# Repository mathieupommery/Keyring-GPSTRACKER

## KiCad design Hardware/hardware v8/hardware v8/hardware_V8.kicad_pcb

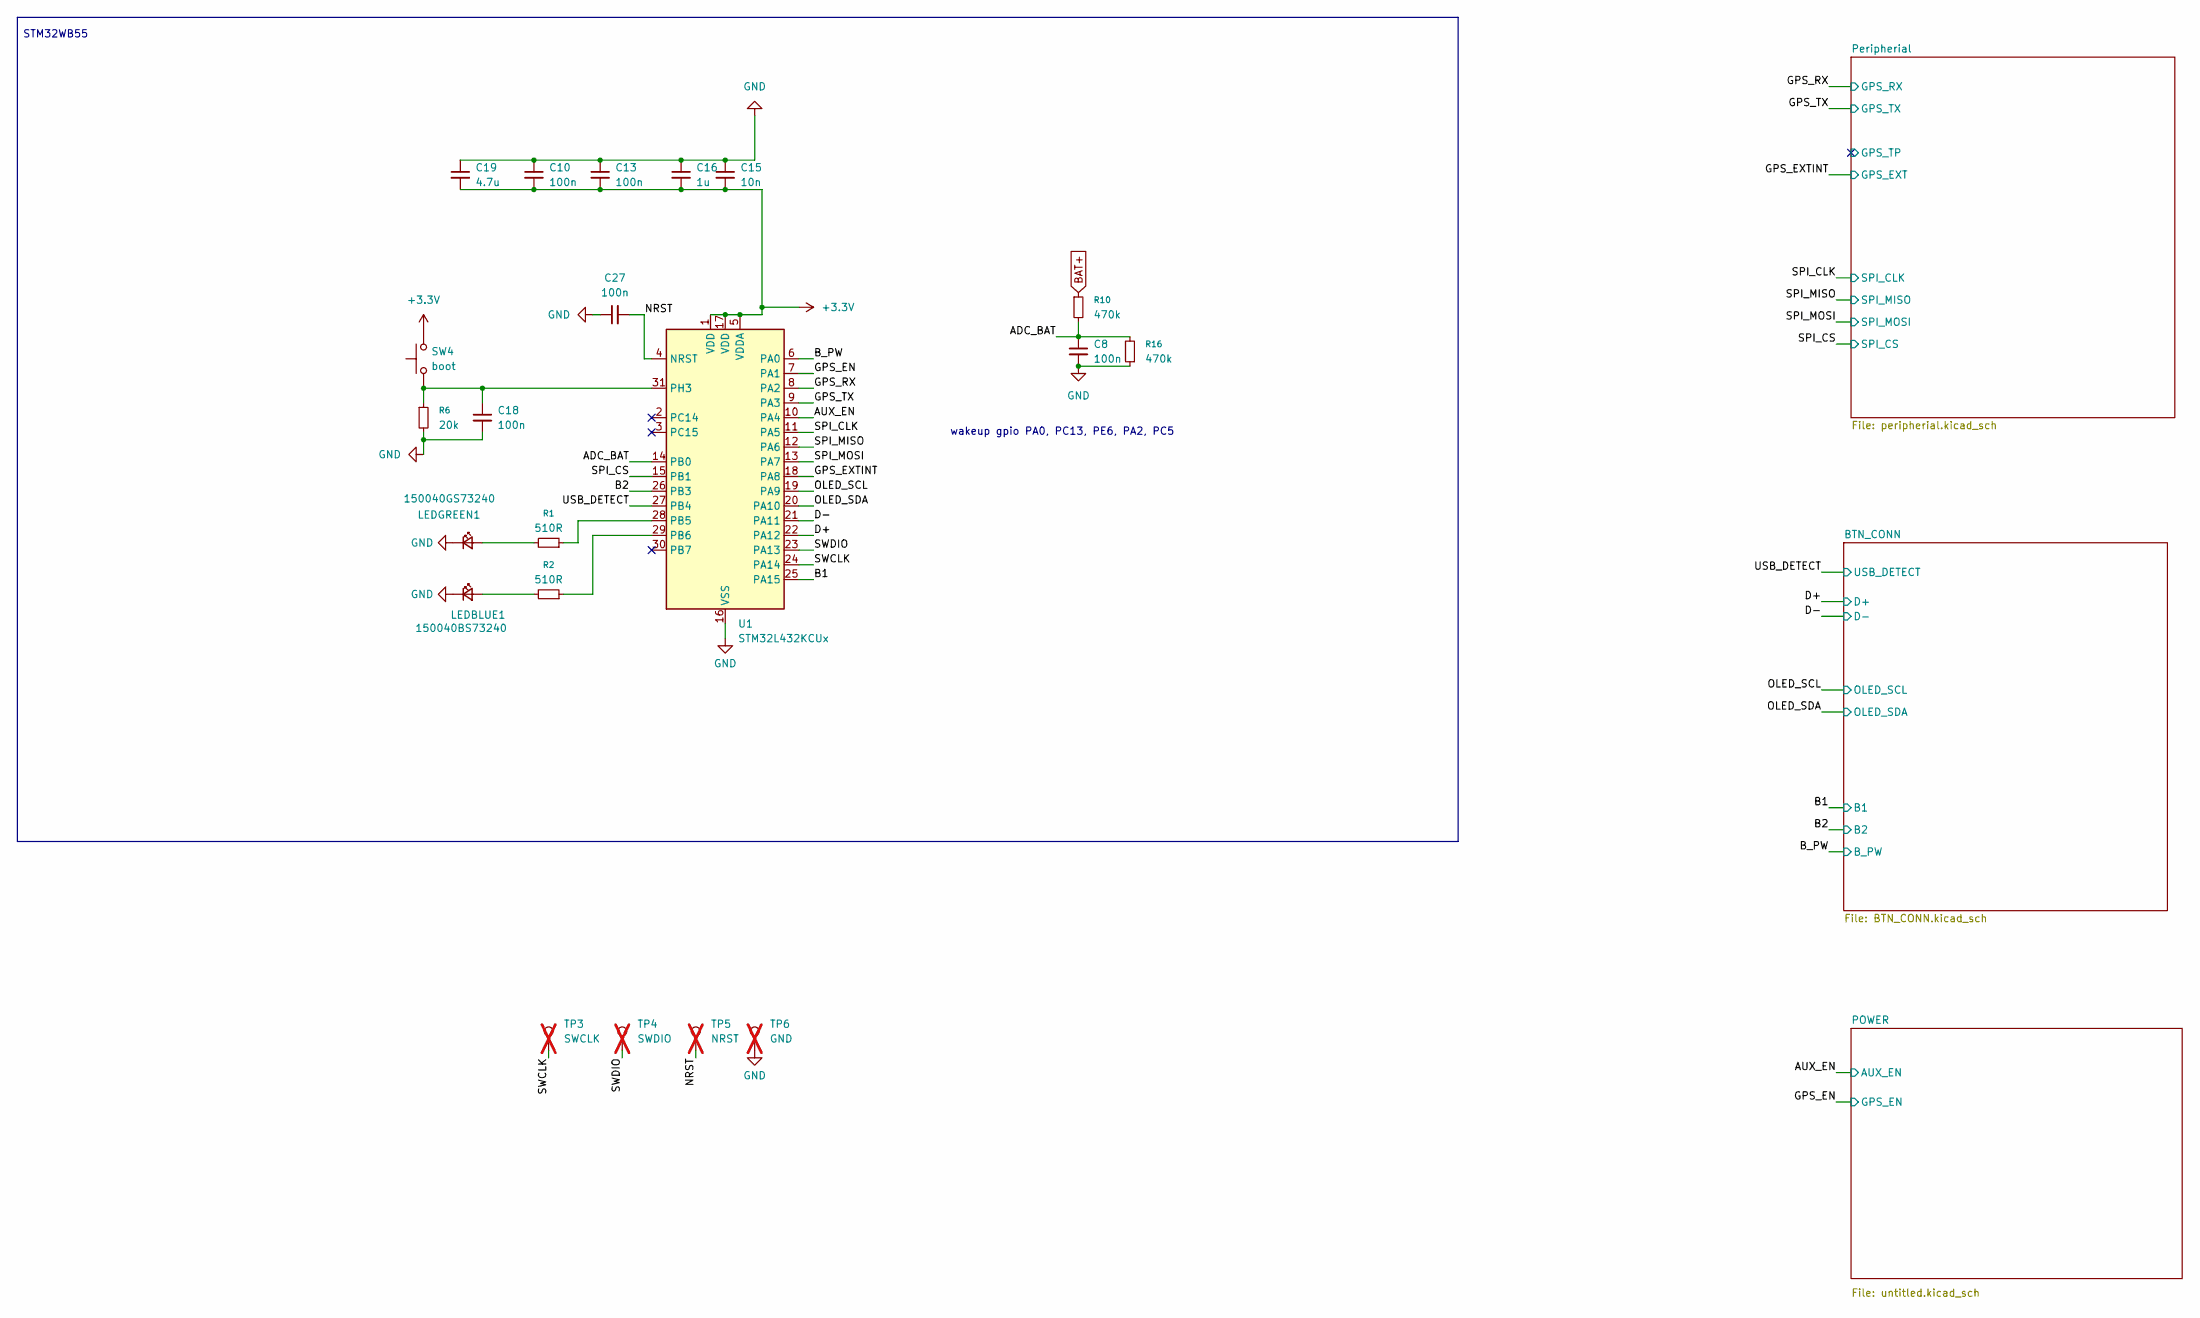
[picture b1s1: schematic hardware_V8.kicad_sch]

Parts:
C8, C10, C13, C18, C27: 100n; C_0201_0603Metric_Pad0.64x0.40mm_HandSolder
C15: 10n; C_0201_0603Metric_Pad0.64x0.40mm_HandSolder
C16: 1u; C_0402_1005Metric
C19: 4.7u; C_0402_1005Metric
LEDBLUE1: 150040BS73240; LED_0402_1005Metric; Manufacturer_Part_Number 150040BS73240; Mouser Part Number 710-150040BS73240
LEDGREEN1: 150040GS73240; LED_0402_1005Metric; Manufacturer_Part_Number 150040GS73240; Mouser Part Number 710-150040GS73240
R1, R2: 510R; R_0201_0603Metric_Pad0.64x0.40mm_HandSolder; Mouser Part Number 603-RC0201JR-07510RL
R6: 20k; R_0201_0603Metric_Pad0.64x0.40mm_HandSolder; Mouser Part Number 603-AC0201FR-0720KL
R10, R16: 470k; R_0201_0603Metric_Pad0.64x0.40mm_HandSolder; Mouser Part Number 603-AC0201FR-07470KL
SW4: boot; KXT341LHS; Mouser Part Number 611-KXT341LHS
TP3: SWCLK; pad_0.7mm; not fitted
TP4: SWDIO; pad_0.7mm; not fitted
TP5: NRST; pad_0.7mm; not fitted
TP6: GND; pad_0.7mm; not fitted
U1: STM32L432KCUx; QFN-32-1EP_5x5mm_P0.5mm_EP3.45x3.45mm; Mouser Part Number 511-STM32L432KCU6

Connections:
+3.3V: C10.2, C13.2, C15.2, C16.2, C19.2, SW4.2, U1.1 (VDD), U1.5 (VDDA), U1.17 (VDD); also elsewhere on the board
/ADC_BAT: C8.1, R10.2, R16.2, U1.14 (PB0)
/AUX_EN: U1.10 (PA4); also elsewhere on the board
/B1: U1.25 (PA15); also elsewhere on the board
/B2: U1.26 (PB3); also elsewhere on the board
/B_PW: U1.6 (PA0); also elsewhere on the board
/D+: U1.22 (PA12); also elsewhere on the board
/D-: U1.21 (PA11); also elsewhere on the board
/GPS_EN: U1.7 (PA1); also elsewhere on the board
/GPS_EXTINT: U1.18 (PA8); also elsewhere on the board
/GPS_RX: U1.8 (PA2); also elsewhere on the board
/GPS_TX: U1.9 (PA3); also elsewhere on the board
/NRST: C27.2, TP5.1, U1.4 (NRST)
/OLED_SCL: U1.19 (PA9); also elsewhere on the board
/OLED_SDA: U1.20 (PA10); also elsewhere on the board
/SPI_CLK: U1.11 (PA5); also elsewhere on the board
/SPI_CS: U1.15 (PB1); also elsewhere on the board
/SPI_MISO: U1.12 (PA6); also elsewhere on the board
/SPI_MOSI: U1.13 (PA7); also elsewhere on the board
/SWCLK: TP3.1, U1.24 (PA14)
/SWDIO: TP4.1, U1.23 (PA13)
/USB_DETECT: U1.27 (PB4); also elsewhere on the board
BAT+: R10.1; also elsewhere on the board
GND: C8.2, C10.1, C13.1, C15.1, C16.1, C18.2, C19.1, C27.1, LEDBLUE1.1 (K), LEDGREEN1.1 (K), R6.2, R16.1, TP6.1, U1.16 (VSS), U1.32 (VSS), U1.33 (VSS); also elsewhere on the board
unnamed: LEDBLUE1.2 (A), R2.2
unnamed: LEDGREEN1.2 (A), R1.2
unnamed: R1.1, U1.28 (PB5)
unnamed: R2.1, U1.29 (PB6)
unnamed: C18.1, R6.1, SW4.1, U1.31 (PH3)

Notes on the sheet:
STM32WB55
wakeup gpio PA0, PC13, PE6, PA2, PC5

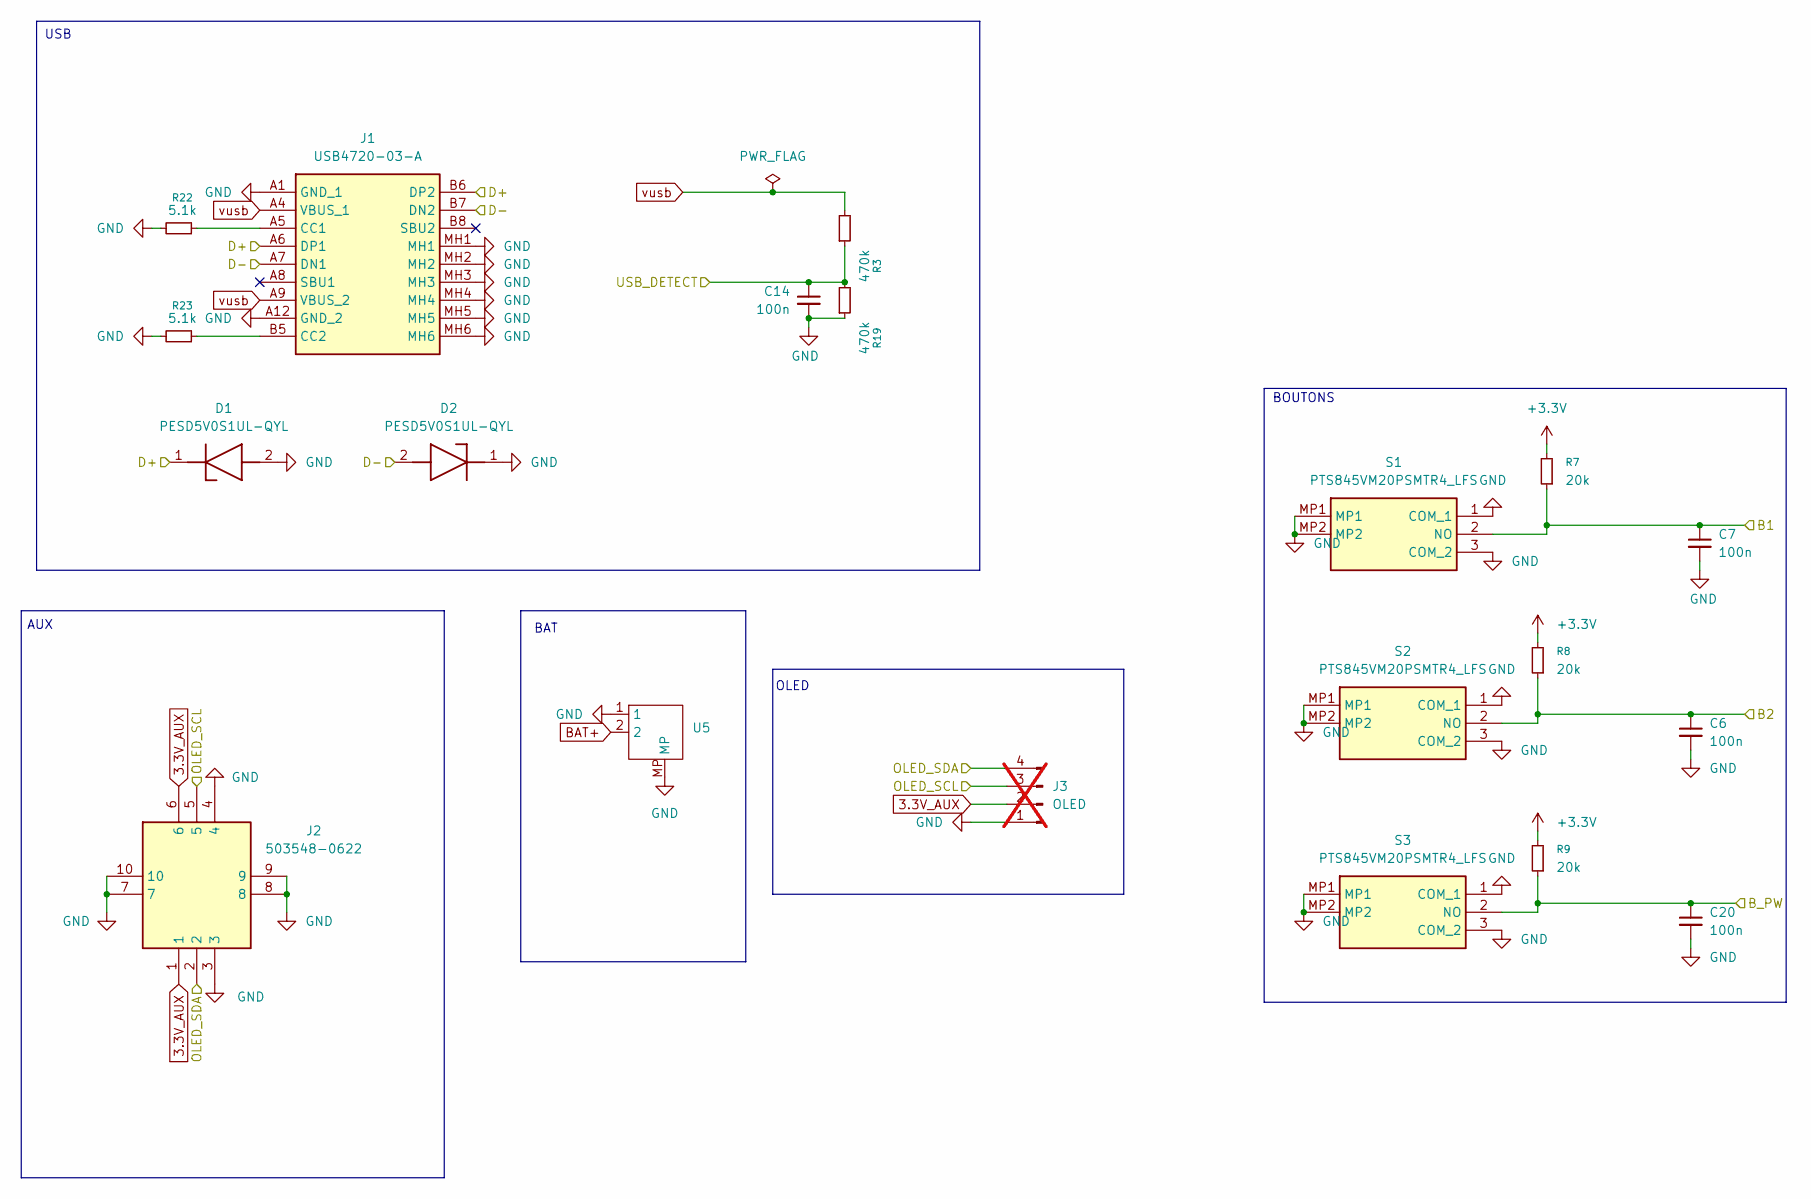
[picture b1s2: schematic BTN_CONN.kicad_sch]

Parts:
C6, C7, C14, C20: 100n; C_0201_0603Metric_Pad0.64x0.40mm_HandSolder
D1, D2: PESD5V0S1UL-QYL; PESD5V0S1ULQYL; Manufacturer_Part_Number PESD5V0S1UL-QYL; Mouser Part Number 771-PESD5V0S1UL-QYL
J1: USB4720-03-A; USB472003A; Manufacturer_Part_Number USB4720-03-A; Mouser Part Number 640-USB472003A
J2: 503548-0622; 5035480622; Manufacturer_Part_Number 503548-0622; Mouser Part Number 538-503548-0622
J3: OLED; PinSocket_1x04_P2.54mm_Vertical; not fitted
R3, R19: 470k; R_0201_0603Metric_Pad0.64x0.40mm_HandSolder
R7, R8, R9: 20k; R_0201_0603Metric_Pad0.64x0.40mm_HandSolder
R22, R23: 5.1k; R_0201_0603Metric_Pad0.64x0.40mm_HandSolder
S1, S2, S3: PTS845VM20PSMTR4_LFS; PTS845VM20PSMTR4LFS; Manufacturer_Part_Number PTS845VM20PSMTR4 LFS; Mouser Part Number 611-PTS845VM20PSMTR4
U5: JST_SH_BM02B-SRSS-TB_1x02-1MP_P1.00mm_Vertical

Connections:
3.3V_AUX: J2.1, J2.6, J3.2; also elsewhere on the board
+3.3V: R7.2, R8.2, R9.2; also elsewhere on the board
/B1: C7.1, R7.1, S1.2 (NO); also elsewhere on the board
/B2: C6.1, R8.1, S2.2 (NO); also elsewhere on the board
/B_PW: C20.1, R9.1, S3.2 (NO); also elsewhere on the board
/D+: D1.1 (K), J1.A6 (DP1), J1.B6 (DP2); also elsewhere on the board
/D-: D2.2 (A), J1.A7 (DN1), J1.B7 (DN2); also elsewhere on the board
/OLED_SCL: J2.5, J3.3; also elsewhere on the board
/OLED_SDA: J2.2, J3.4; also elsewhere on the board
/USB_DETECT: C14.1, R3.1, R19.2; also elsewhere on the board
BAT+: U5.2; also elsewhere on the board
GND: C6.2, C7.2, C14.2, C20.2, D1.2 (A), D2.1 (K), J1.A1 (GND_1), J1.A12 (GND_2), J1.MH1, J1.MH2, J1.MH3, J1.MH4, J1.MH5, J1.MH6, J2.3, J2.4, J2.7, J2.8, J2.9, J2.10, J3.1, R19.1, R22.2, R23.2, S1.1 (COM_1), S1.3 (COM_2), S1.MP1, S1.MP2, S2.1 (COM_1), S2.3 (COM_2), S2.MP1, S2.MP2, S3.1 (COM_1), S3.3 (COM_2), S3.MP1, S3.MP2, U5.1, U5.MP; also elsewhere on the board
unnamed: J1.A5 (CC1), R22.1
unnamed: J1.B5 (CC2), R23.1
vusb: J1.A4 (VBUS_1), J1.A9 (VBUS_2), R3.2; also elsewhere on the board

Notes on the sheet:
AUX
BOUTONS
USB
OLED
BAT

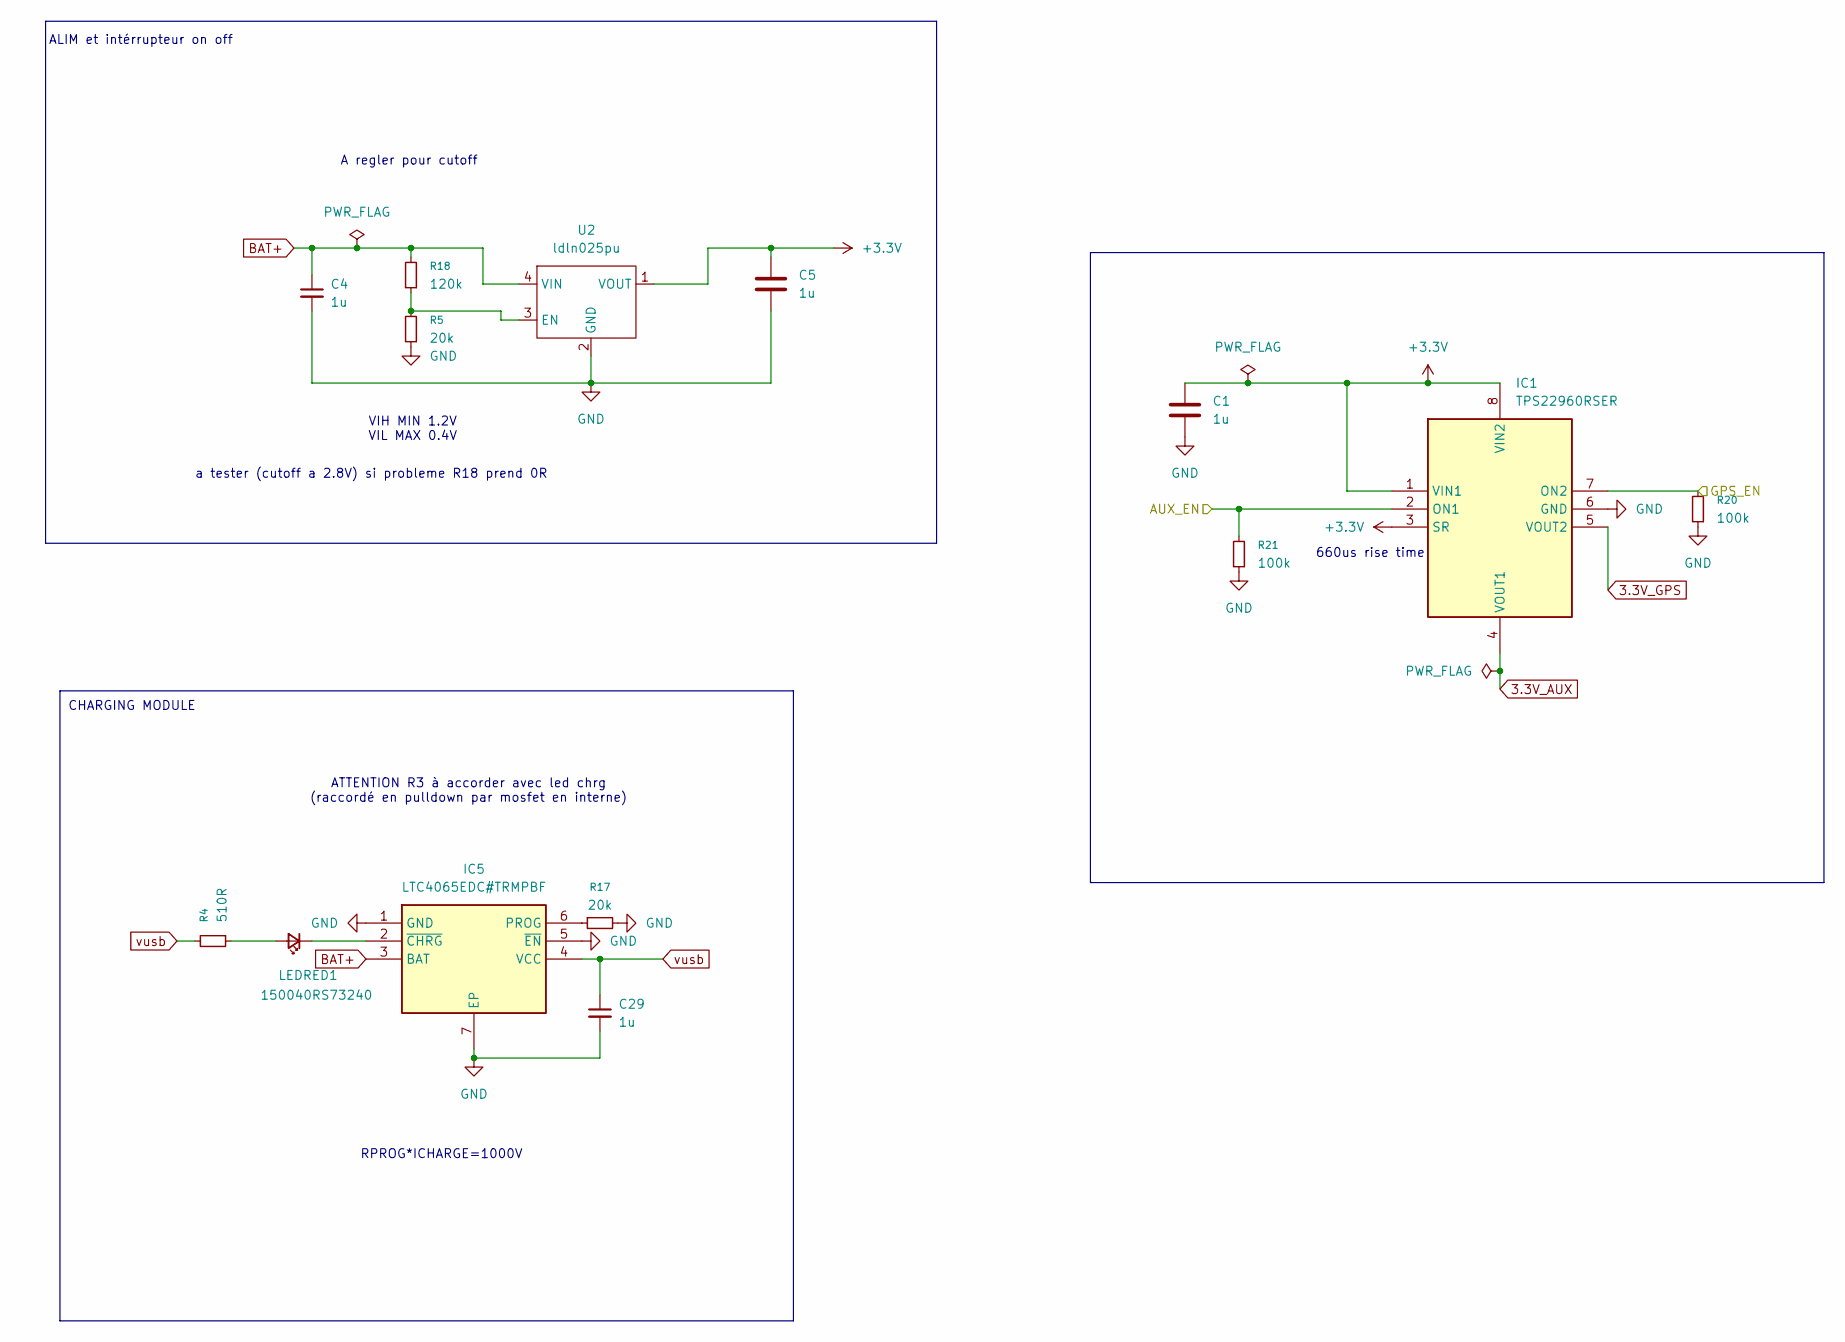
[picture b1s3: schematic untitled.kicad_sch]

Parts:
C1, C4, C5, C29: 1u; C_0402_1005Metric
IC1: TPS22960RSER; Manufacturer_Part_Number TPS22960RSER; Mouser Part Number 595-TPS22960RSER
IC5: LTC4065EDC#TRMPBF; SON50P200X200X80-7N-D; Manufacturer_Part_Number LTC4065EDC#TRMPBF; Mouser Part Number 584-LTC4065EDCTRMPBF
LEDRED1: 150040RS73240; LED_0402_1005Metric; Manufacturer_Part_Number 150040GS73240; Mouser Part Number 710-150040GS73240
R4: 510R; R_0201_0603Metric_Pad0.64x0.40mm_HandSolder
R5, R17: 20k; R_0201_0603Metric_Pad0.64x0.40mm_HandSolder
R18: 120k; R_0201_0603Metric_Pad0.64x0.40mm_HandSolder
R20, R21: 100k; R_0201_0603Metric_Pad0.64x0.40mm_HandSolder
U2: ldln025pu

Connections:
3.3V_AUX: IC1.4 (VOUT1); also elsewhere on the board
3.3V_GPS: IC1.5 (VOUT2); also elsewhere on the board
+3.3V: C1.1, C5.1, IC1.1 (VIN1), IC1.3 (SR), IC1.8 (VIN2), U2.1 (VOUT); also elsewhere on the board
/AUX_EN: IC1.2 (ON1), R21.2; also elsewhere on the board
/GPS_EN: IC1.7 (ON2), R20.2; also elsewhere on the board
BAT+: C4.1, IC5.3 (BAT), R18.2, U2.4 (VIN); also elsewhere on the board
GND: C1.2, C4.2, C5.2, C29.2, IC1.6 (GND), IC5.1 (GND), IC5.5 (~EN), IC5.7 (EP), R5.1, R17.2, R20.1, R21.1, U2.2 (GND); also elsewhere on the board
unnamed: IC5.6 (PROG), R17.1
unnamed: IC5.2 (~CHRG), LEDRED1.1 (K)
unnamed: LEDRED1.2 (A), R4.1
unnamed: R5.2, R18.1, U2.3 (EN)
vusb: C29.1, IC5.4 (VCC), R4.2; also elsewhere on the board

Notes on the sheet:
VIH MIN 1.2V VIL MAX 0.4V
ALIM et intérrupteur on off
A regler pour cutoff
a tester (cutoff a 2.8V) si probleme R18 prend 0R
RPROG*ICHARGE=1000V
ATTENTION R3 à accorder avec led chrg (raccordé en pulldown par mosfet en interne)
CHARGING MODULE
660us rise time

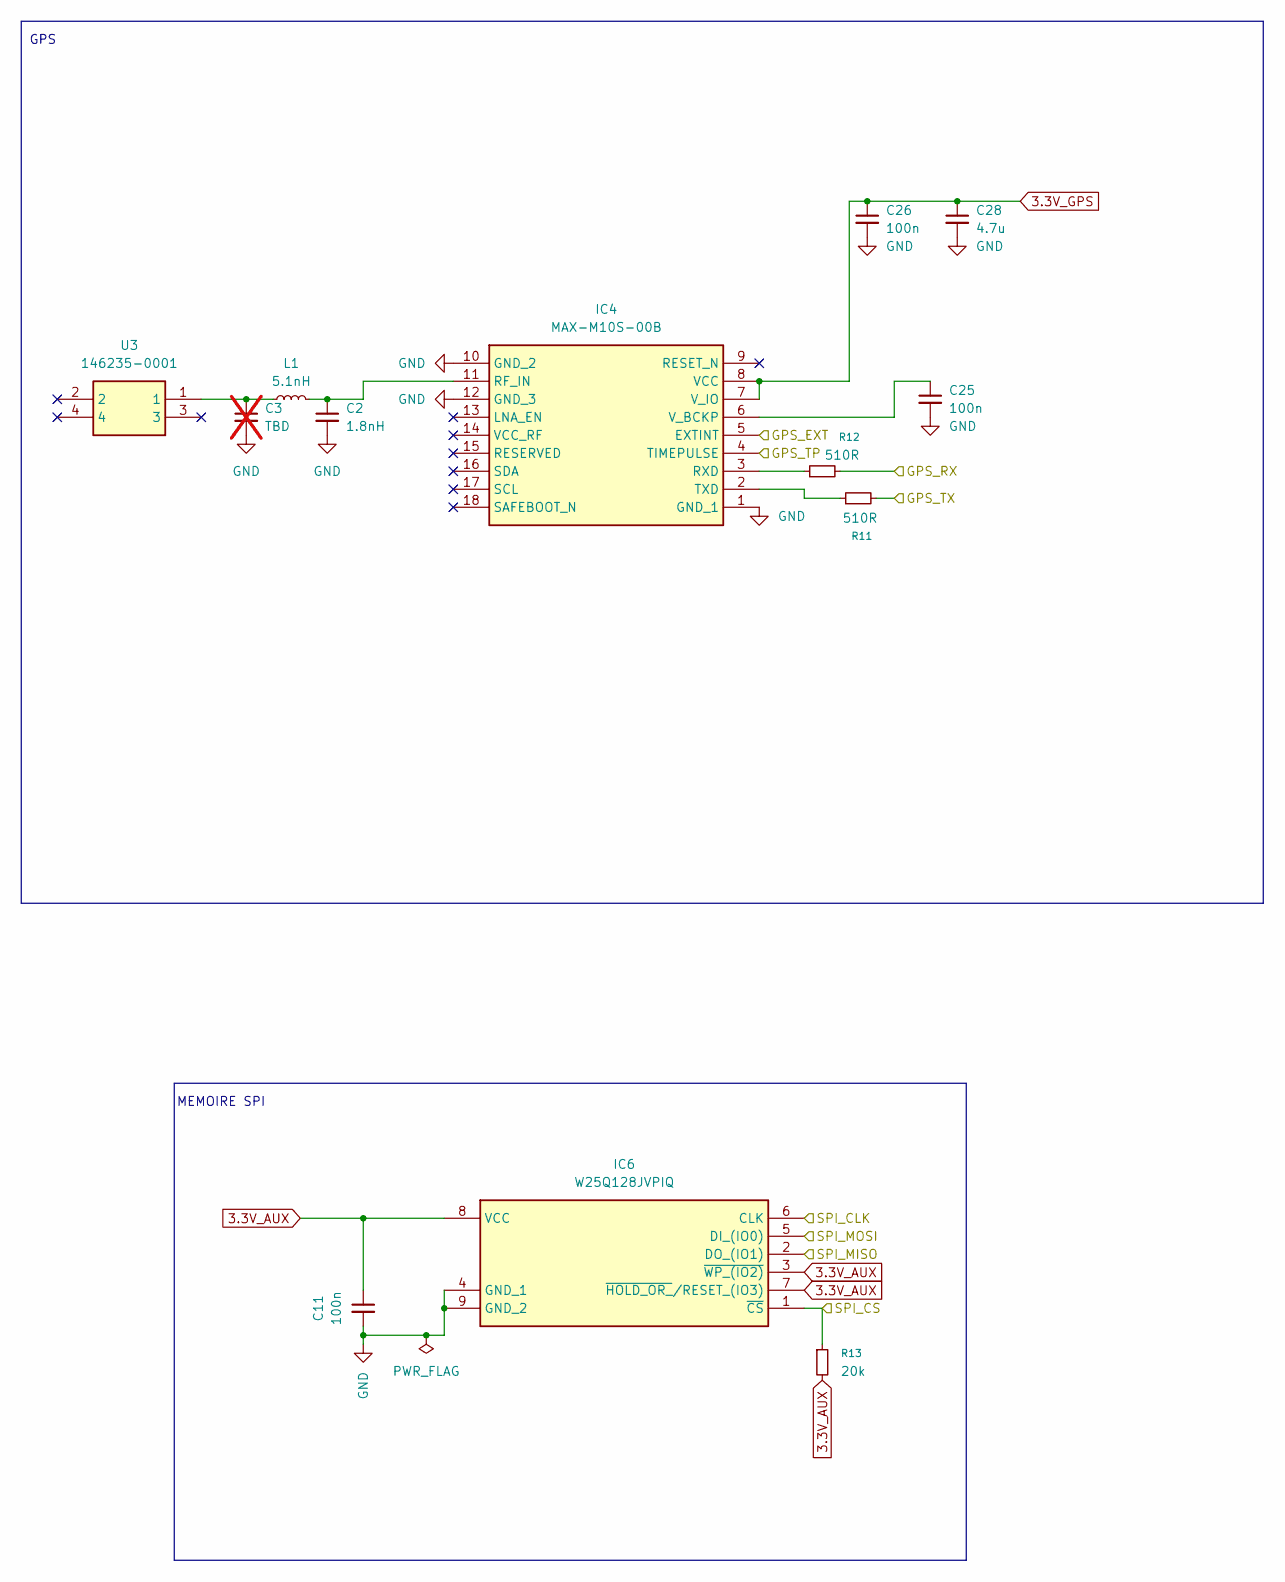
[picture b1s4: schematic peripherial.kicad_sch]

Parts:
C2: 1.8nH; C_0402_1005Metric
C3: TBD; C_0402_1005Metric; not fitted
C11, C25, C26: 100n; C_0201_0603Metric_Pad0.64x0.40mm_HandSolder
C28: 4.7u; C_0402_1005Metric
IC4: MAX-M10S-00B; MAXM10S00B; Manufacturer_Part_Number MAX-M10S-00B; Mouser Part Number 377-MAX-M10S-00B
IC6: W25Q128JVPIQ; SON127P600X500X80-9N-D; Manufacturer_Part_Number W25Q128JVPIQ; Mouser Part Number 454-W25Q128JVPIQ
L1: 5.1nH; L_0402_1005Metric
R11, R12: 510R; R_0201_0603Metric_Pad0.64x0.40mm_HandSolder
R13: 20k; R_0201_0603Metric_Pad0.64x0.40mm_HandSolder
U3: 146235-0001; Manufacturer_Part_Number 146235-0001; Mouser Part Number 538-146235-0001

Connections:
3.3V_AUX: C11.1, IC6.3 (~WP_(IO2)), IC6.7 (~HOLD_OR_/RESET_(IO3)), IC6.8 (VCC), R13.2; also elsewhere on the board
3.3V_GPS: C26.1, C28.1, IC4.7 (V_IO), IC4.8 (VCC); also elsewhere on the board
/GPS_EXTINT: IC4.5 (EXTINT); also elsewhere on the board
/GPS_RX: R12.2; also elsewhere on the board
/GPS_TX: R11.2; also elsewhere on the board
/Peripherial/GPS_TP: IC4.4 (TIMEPULSE)
/SPI_CLK: IC6.6 (CLK); also elsewhere on the board
/SPI_CS: IC6.1 (~CS), R13.1; also elsewhere on the board
/SPI_MISO: IC6.2 (DO_(IO1)); also elsewhere on the board
/SPI_MOSI: IC6.5 (DI_(IO0)); also elsewhere on the board
GND: C2.2, C3.2, C11.2, C25.2, C26.2, C28.2, IC4.1 (GND_1), IC4.10 (GND_2), IC4.12 (GND_3), IC6.4 (GND_1), IC6.9 (GND_2); also elsewhere on the board
unnamed: C3.1, L1.1, U3.1
unnamed: C2.1, IC4.11 (RF_IN), L1.2
unnamed: IC4.3 (RXD), R12.1
unnamed: IC4.2 (TXD), R11.1
unnamed: C25.1, IC4.6 (V_BCKP)

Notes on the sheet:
MEMOIRE SPI
GPS

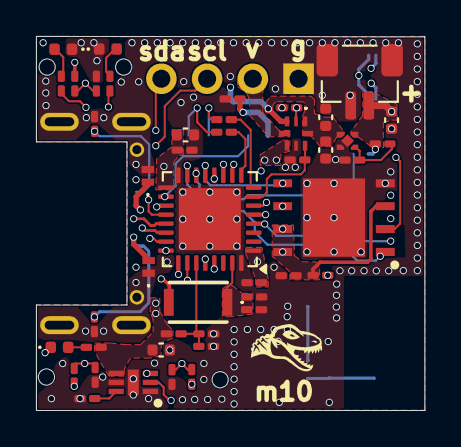
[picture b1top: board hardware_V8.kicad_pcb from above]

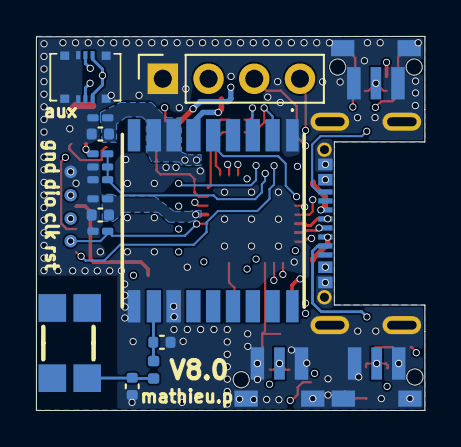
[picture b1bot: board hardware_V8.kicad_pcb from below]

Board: 6 copper layers, 21.6 x 20.8 mm, 68 parts (23 on the bottom side), 43 nets.

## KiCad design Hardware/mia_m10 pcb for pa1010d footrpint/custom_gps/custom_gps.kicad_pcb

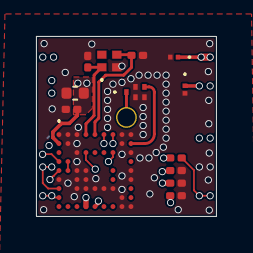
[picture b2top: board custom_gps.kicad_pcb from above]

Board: 6 copper layers, 10.0 x 10.0 mm, 14 parts (1 on the bottom side), 16 nets.

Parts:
C1, C2, C3: 100n; C_0201_0603Metric
C4: 10u; C_0402_1005Metric
C5, C6: 2.5p; C_0201_0603Metric
Connpa1010d1: PA1010D
D1, D2: RCLAMP3521ZATFT
FL1: SF14-1582M5UUD2; SF141582M5UUD2
IC1: MIA-M10Q-00B; MIAM10Q00B
J1: 830107834801
R2: DNP; R_0201_0603Metric
R3: 4.7k; R_0201_0603Metric

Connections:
+3.3V: C1.1, C3.1, C4.1, Connpa1010d1.10 (VCC), D1.1, IC1.B1 (VCC), IC1.J4 (V_IO), R3.1
EXTINT: Connpa1010d1.8 (WAKE_UP), IC1.A6 (EXTINT)
GND: C1.2, C2.2, C3.2, C4.2, C5.2, C6.2, Connpa1010d1.7 (GND), D1.2, D2.2, FL1.2 (GND_1), FL1.3 (GND_2), FL1.5 (GND_3), IC1.A1 (GND_1), IC1.A2 (GND_2), IC1.A3 (GND_3), IC1.A8 (GND_4), IC1.A9 (GND_5), IC1.B2 (GND_6), IC1.B8 (GND_7), IC1.C3 (GND_8), IC1.C9 (GND_9), IC1.E3 (GND_10), IC1.E4 (GND_11), IC1.E9 (GND_12), IC1.F1 (GND_13), IC1.F3 (GND_14), IC1.F4 (GND_15), IC1.F9 (RESERVED_7), IC1.G3 (GND_16), IC1.G4 (GND_17), IC1.G5 (GND_18), IC1.G6 (GND_19), IC1.G7 (RESERVED_8), IC1.H8 (GND_20), IC1.J8 (GND_21), IC1.J9 (GND_22), J1.2 (GND(LID)), R2.2
unnamed: Connpa1010d1.11 (RF_ANT), FL1.1 (INPUT)
unnamed: IC1.D2 (RESERVED_3), IC1.E2 (RESERVED_5)
unnamed: IC1.C7 (SAFEBOOT_N), R2.1
RESET: Connpa1010d1.6 (NRESET), IC1.C4 (RESET_N), R3.2
RF_IN: FL1.4 (OUTPUT), IC1.B9 (RF_IN)
RTC_IN: C5.1, IC1.A4 (RTC_I), J1.1 (CRYSTAL_1)
RTC_OUT: C6.1, IC1.A5 (RTC_O), J1.3 (CRYSTAL_2)
RX: Connpa1010d1.5 (RX), IC1.H1 (RX)
SCL: Connpa1010d1.2 (I2C_SCL), IC1.E1 (SCL)
SDA: Connpa1010d1.1 (I2C_SDA), IC1.D1 (SDA)
TIMEPULSE: Connpa1010d1.3 (1PPS), IC1.A7 (TIMEPULSE)
TX: Connpa1010d1.4 (TX), IC1.G1 (TX)
VBACKUP: C2.1, Connpa1010d1.9 (VBACKUP), D2.1, IC1.J5 (V_BCKP)
